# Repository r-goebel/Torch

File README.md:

# LED torch
On the EH18 I got the idea to put an LED strip on a cardboard tube to use the full 5m without having to unwind and wind it all the time. The connections for 5V will be installed permanently and can easily be plugged in later. For the effects an ESP is installed, which is also powered via the 5V connection. 

## Material
  * cardboard shipping roll (D=80mm; L=600mm(?))
  * 5m LED Strip (WS2812b; Amazon)
  * Wemos D1 mini (ESP8266)
  * 3 Capacitor (1000 µF)
  * Resistor 470 Ohm
  * Resistor 10k Ohm 
  * Diode
  * Cable (For power and data)
  * Power supply 5V (up to now max. 2A --> Maximum brightness not higher than 20)
  * XT30 for connection between power supply and torch
  * MR30 for connection between Power suppli/PCB and the LEDstrip
  
  For an advanced look:
  * Laser-cutted wood box (housing for PCB and Torch-Mount)
  * Lamp Foil and Sandwich paper for light scattering

## Effects
This project additionally needs the Effect-library: https://github.com/r-goebel/Effects

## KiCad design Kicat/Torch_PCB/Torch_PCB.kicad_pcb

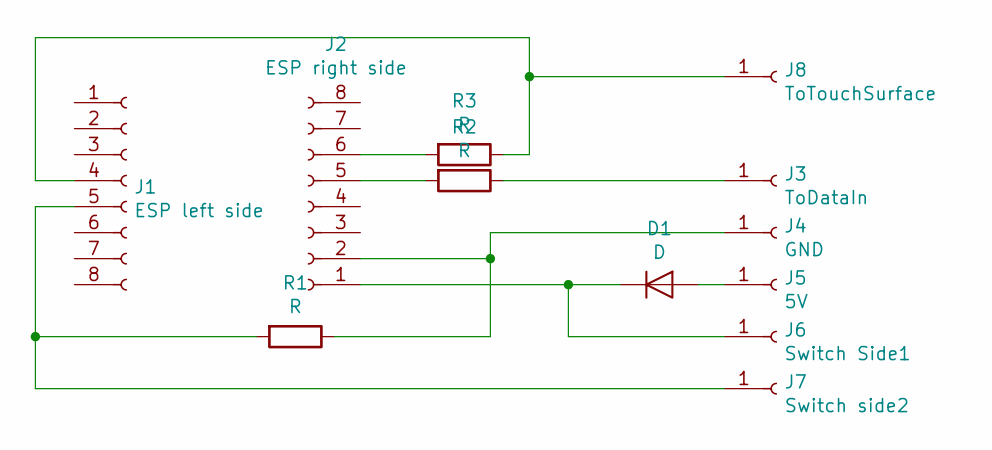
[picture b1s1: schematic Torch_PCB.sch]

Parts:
D1: D; D_5W_P10.16mm_Horizontal
J1: ESP left side; PinSocket_1x08_P2.54mm_Vertical
J2: ESP right side; PinSocket_1x08_P2.54mm_Vertical
J3: ToDataIn; PinSocket_1x01_P2.54mm_Vertical
J4: GND; PinSocket_1x01_P2.54mm_Vertical
J5: 5V; PinSocket_1x01_P2.54mm_Vertical
J6: Switch Side1; PinSocket_1x01_P2.54mm_Vertical
J7: Switch side2; PinSocket_1x01_P2.54mm_Vertical
J8: ToTouchSurface; PinSocket_1x01_P2.54mm_Vertical
R1, R2, R3: R; R_Axial_DIN0207_L6.3mm_D2.5mm_P10.16mm_Horizontal

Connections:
unnamed: D1.1 (K), J2.1, J6.1
unnamed: D1.2 (A), J5.1
unnamed: J1.4, J8.1, R3.1
unnamed: J1.5, J7.1, R1.2
unnamed: J2.2, J4.1, R1.1
unnamed: J2.5, R2.2
unnamed: J2.6, R3.2
unnamed: J3.1, R2.1

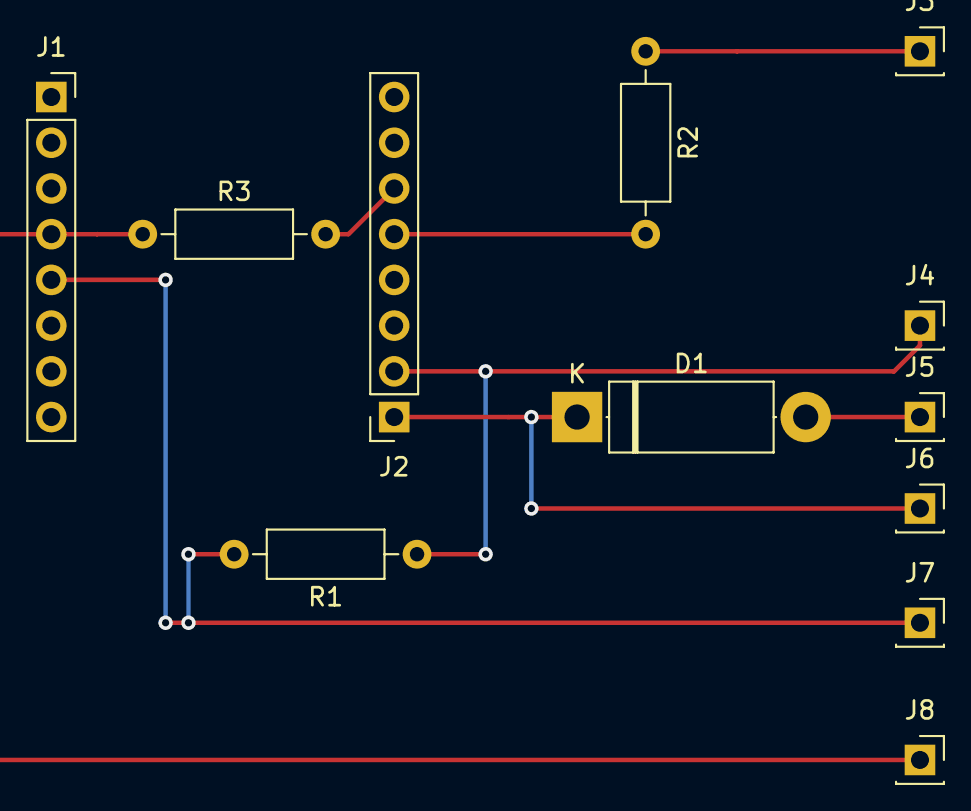
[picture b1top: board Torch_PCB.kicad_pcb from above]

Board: 2 copper layers, 12 parts (0 on the bottom side), 8 nets.

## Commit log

2019-09-28 Basisprogramm welches erstmal mit einem Programm und ohne Wlan läuft
2019-09-28 läuft nun mit einem Effekt aus starcalcs NeoPattern
2019-09-28 Effekte eingebaut
2019-09-28 Ende des Tages
2019-09-29 Programmwahl mittels Taster eingebaut
2019-10-28 diverses und Basic code für ein effect
2019-10-28 Scanner/Cyclon Effect hinzugefügt
2019-10-28 mehr effekte, laufen aber noch nicht alle sinnvoll
2019-11-01 Meteor auf senkrecht umgestellt
2019-11-01 noch etwas an parametern geschraubt, Feuer brauchbar aber nicht optimal
2019-11-01 Feuer ist nun Funktionsbereit
2019-11-01 added rain effect
2019-11-01 added Plasma effect
2019-11-02 Renamed Kicat-files
2019-11-02 Renamed files
2019-11-02 „README.md“ hinzufügen
2019-11-02 irgendwie noch falche Files vorhanden
2019-11-02 Renamed Torch sketch
2019-11-02 Basic sketch for TCP communication
2019-11-03 added gitignore to hide WiFiSettings
2019-11-03 externalized funktion for WifiSetup
2019-11-03 Communication with client finished
2019-11-03 Merged basic_TCP in Torch
2019-11-03 Fixed Translation, better Ideas needed
2019-11-04 Verbesserung in Kommunication durch vergleich mit Effect Liste
2019-11-04 New Version of Communication
2019-11-05 renamed some files
2019-11-05 started from scratch for updated version of torchcode, parallelisation
2019-11-05 started with effect library
2019-11-05 added effect FadeInOut
2019-11-06 added cyclone effect
2019-11-06 Using Increment in both directions in Fade
2019-11-06 Twinkle and Sparkle added
2019-11-06 included Effect selection based on input
2019-11-06 enabled random selection and limited color selection
2019-11-06 missed to put change indicator
2019-11-07 removed camel case in effect list
2019-11-09 Added color wipe and included rainbow cycle
2019-11-09 changed code for twinkle, problem with crashes of esp
2019-11-09 corrected typo
2019-11-09 not each pixel was turned off in twinkle
2019-11-09 added fire to effecrs
2019-11-09 added comment on fire
2019-11-09 changed data type of Positions
2019-11-09 changed effect size for twinkle
2019-11-09 added theater rainbow effect
2019-11-10 added metor rain, only one at a time
2019-11-10 set direction for twinkle effects, fixes chrashes
2019-11-10 added rain to effects
2019-11-10 fixed missing pixel in second row
2019-11-10 „README.md“ ändern
2019-11-10 started with code for marble
2019-11-11 finished marble physics
2019-11-19 Laser datei eingefügt
2019-11-19 multiple meteors and references
2019-11-25 Kicat files updated
2019-11-25 files laser final
2019-12-03 updatet sketches for laser
2019-12-03 added Touch sensor
2019-12-03 removed Serial print
2019-12-03 changed measure for Positioning
2019-12-03 Added touch to Kicat files
2019-12-09 reset touch intervall and higher brightness
2019-12-09 replaced Touch by common switch due to Malefunctions
2019-12-09 random selection of first effect
2019-12-09 deleted touch from Kicat files
2019-12-09 set maximum time interval for Wlan connection
2019-12-09 Externalized Effects in separate repo
2019-12-27 ice fire added
2020-01-05 added heartbeat
2020-01-12 paar änderungen
2020-12-21 added config to gitignore
2021-11-21 added initial file for platformio
2021-11-21 created new platformio project
2021-11-28 changed torch to platformio and homie 30
2021-12-12 now rettrieves last state, effect and color from influxdb via node red
2021-12-12 added Node res flow
